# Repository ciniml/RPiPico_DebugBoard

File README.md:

# Raspberry Pi Pico Debug Board

## 概要

Raspberry Pi Pico用のデバッグ用ボード。

ブレッドボードを使うほどでもないが、デバッガはつなぎたい もしくはPicoprobeのデバッグ・ユニットとして使いたい場合に便利なように配線を引き出すためのボードです。

[回路図(PDF)](./RPiPico_SimpleBoard.pdf)

## 特徴

* リセット・スイッチ
* Picoprobe用SWD + UART TX/RXコネクタ
* デバッガ接続用ポゴピン実装スルーホール
* 全信号2列引き出し
  * 信号引き出しつつ、ロジックアナライザを接続可能

## 使用例

### RPi Picoを2枚つかったSWDデバッグ

上側のデバッグ基板のファームウェアとして [`rust-dap`](https://github.com/ciniml/rust-dap) を書き込み。下側のRaspberry Pi PicoにLチカファームウェアをデバッガ経由で書き込んでデバッグ中

## ライセンス

### 基板本体
CC BY 4.0
<br />This work is licensed under a <a rel="license" href="http://creativecommons.org/licenses/by/4.0/">Creative Commons Attribution 4.0 International License</a>.

### ライブラリ (local.kicad_sym, local.pretty以下)

一部のコンポーネントがKiCad標準のコンポーネントを改変したものであるため、そのライセンス (CC BY-SA 4.0) が適用される

また、Raspberry Pi Picoの3Dモデルも、CC BY-SA 4.0に基いて配布されているので同様である。
https://www.raspberrypi.com/documentation/microcontrollers/raspberry-pi-pico.html

CC BY-SA 4.0
<br />This work is licensed under a <a rel="license" href="http://creativecommons.org/licenses/by-sa/4.0/">Creative Commons Attribution-ShareAlike 4.0 International License</a>.

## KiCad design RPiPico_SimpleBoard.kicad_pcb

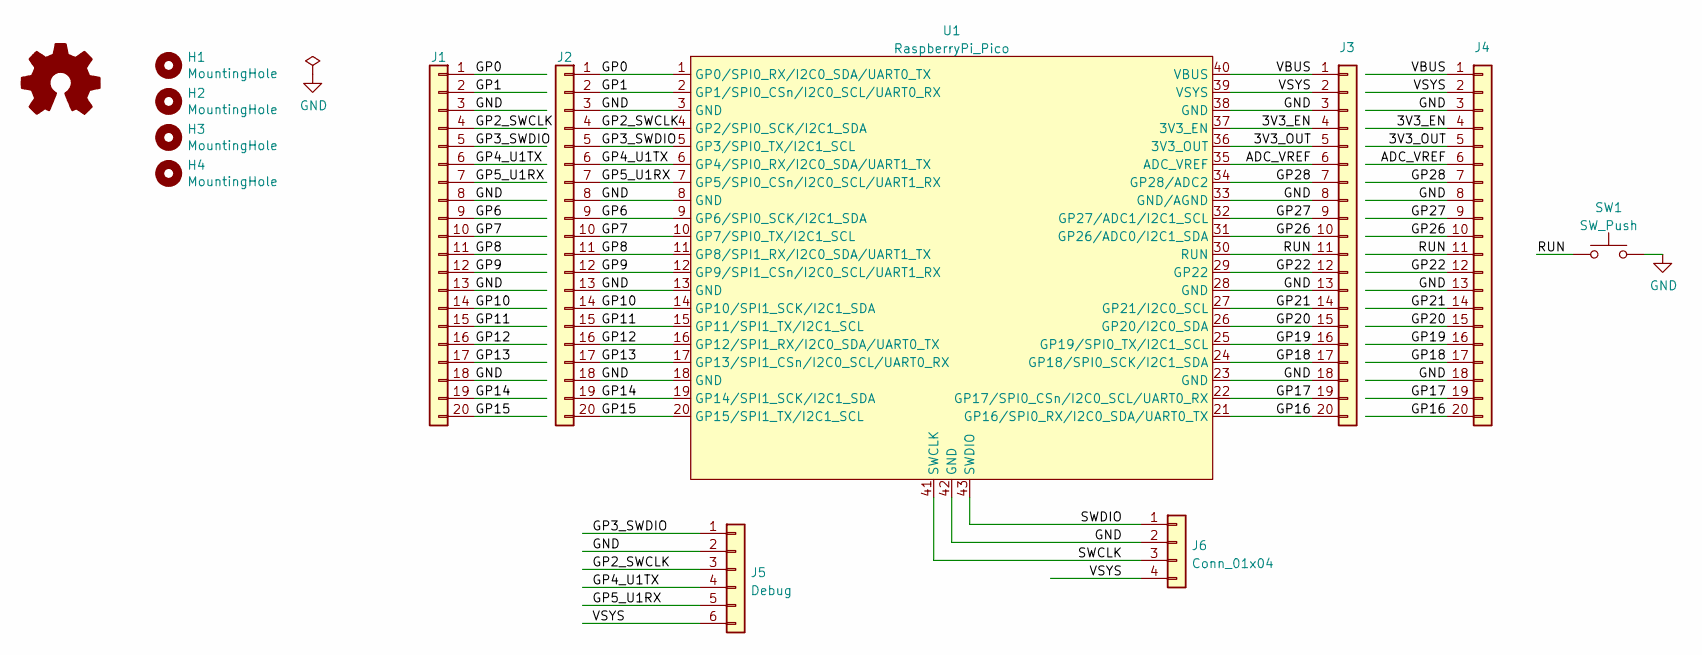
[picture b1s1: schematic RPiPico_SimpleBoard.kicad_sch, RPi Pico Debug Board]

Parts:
H1, H2, H3, H4: MountingHole; MountingHole_3.2mm_M3
J1, J4: Conn_01x20; PinHeader_1x20_P2.54mm_Vertical_Narrow
J2, J3: Conn_01x20; PinSocket_1x20_P2.54mm_Vertical_Narrow
J5: Debug; PinHeader_1x06_P2.54mm_Horizontal_Narrow
J6: Conn_01x04; PinHeader_1x04_P2.54mm_Vertical
LOGO1: Logo_Open_Hardware_Small; logo
SW1: SW_Push; TVBP06-BN043XX-B
U1: RaspberryPi_Pico; Raspberry_Pi_Pico_TH_SMD_SWD

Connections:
/3V3_EN: J3.4, J4.4, U1.37 (3V3_EN)
/3V3_OUT: J3.5, J4.5, U1.36 (3V3_OUT)
/ADC_VREF: J3.6, J4.6, U1.35 (ADC_VREF)
/GP0: J1.1, J2.1, U1.1 (GP0/SPI0_RX/I2C0_SDA/UART0_TX)
/GP1: J1.2, J2.2, U1.2 (GP1/SPI0_CSn/I2C0_SCL/UART0_RX)
/GP2_SWCLK: J1.4, J2.4, J5.3, U1.4 (GP2/SPI0_SCK/I2C1_SDA)
/GP3_SWDIO: J1.5, J2.5, J5.1, U1.5 (GP3/SPI0_TX/I2C1_SCL)
/GP4_U1TX: J1.6, J2.6, J5.4, U1.6 (GP4/SPI0_RX/I2C0_SDA/UART1_TX)
/GP5_U1RX: J1.7, J2.7, J5.5, U1.7 (GP5/SPI0_CSn/I2C0_SCL/UART1_RX)
/GP6: J1.9, J2.9, U1.9 (GP6/SPI0_SCK/I2C1_SDA)
/GP7: J1.10, J2.10, U1.10 (GP7/SPI0_TX/I2C1_SCL)
/GP8: J1.11, J2.11, U1.11 (GP8/SPI1_RX/I2C0_SDA/UART1_TX)
/GP9: J1.12, J2.12, U1.12 (GP9/SPI1_CSn/I2C0_SCL/UART1_RX)
/GP10: J1.14, J2.14, U1.14 (GP10/SPI1_SCK/I2C1_SDA)
/GP11: J1.15, J2.15, U1.15 (GP11/SPI1_TX/I2C1_SCL)
/GP12: J1.16, J2.16, U1.16 (GP12/SPI1_RX/I2C0_SDA/UART0_TX)
/GP13: J1.17, J2.17, U1.17 (GP13/SPI1_CSn/I2C0_SCL/UART0_RX)
/GP14: J1.19, J2.19, U1.19 (GP14/SPI1_SCK/I2C1_SDA)
/GP15: J1.20, J2.20, U1.20 (GP15/SPI1_TX/I2C1_SCL)
/GP16: J3.20, J4.20, U1.21 (GP16/SPI0_RX/I2C0_SDA/UART0_TX)
/GP17: J3.19, J4.19, U1.22 (GP17/SPI0_CSn/I2C0_SCL/UART0_RX)
/GP18: J3.17, J4.17, U1.24 (GP18/SPI0_SCK/I2C1_SDA)
/GP19: J3.16, J4.16, U1.25 (GP19/SPI0_TX/I2C1_SCL)
/GP20: J3.15, J4.15, U1.26 (GP20/I2C0_SDA)
/GP21: J3.14, J4.14, U1.27 (GP21/I2C0_SCL)
/GP22: J3.12, J4.12, U1.29 (GP22)
/GP26: J3.10, J4.10, U1.31 (GP26/ADC0/I2C1_SDA)
/GP27: J3.9, J4.9, U1.32 (GP27/ADC1/I2C1_SCL)
/GP28: J3.7, J4.7, U1.34 (GP28/ADC2)
/RUN: J3.11, J4.11, SW1.1, U1.30 (RUN)
/SWCLK: J6.3, U1.41 (SWCLK)
/SWDIO: J6.1, U1.43 (SWDIO)
/VBUS: J3.1, J4.1, U1.40 (VBUS)
/VSYS: J3.2, J4.2, J5.6, J6.4, U1.39 (VSYS)
GND: J1.3, J1.8, J1.13, J1.18, J2.3, J2.8, J2.13, J2.18, J3.3, J3.8, J3.13, J3.18, J4.3, J4.8, J4.13, J4.18, J5.2, J6.2, SW1.2, U1.3 (GND), U1.8 (GND), U1.13 (GND), U1.18 (GND), U1.23 (GND), U1.28 (GND), U1.33 (GND/AGND), U1.38 (GND), U1.42 (GND)

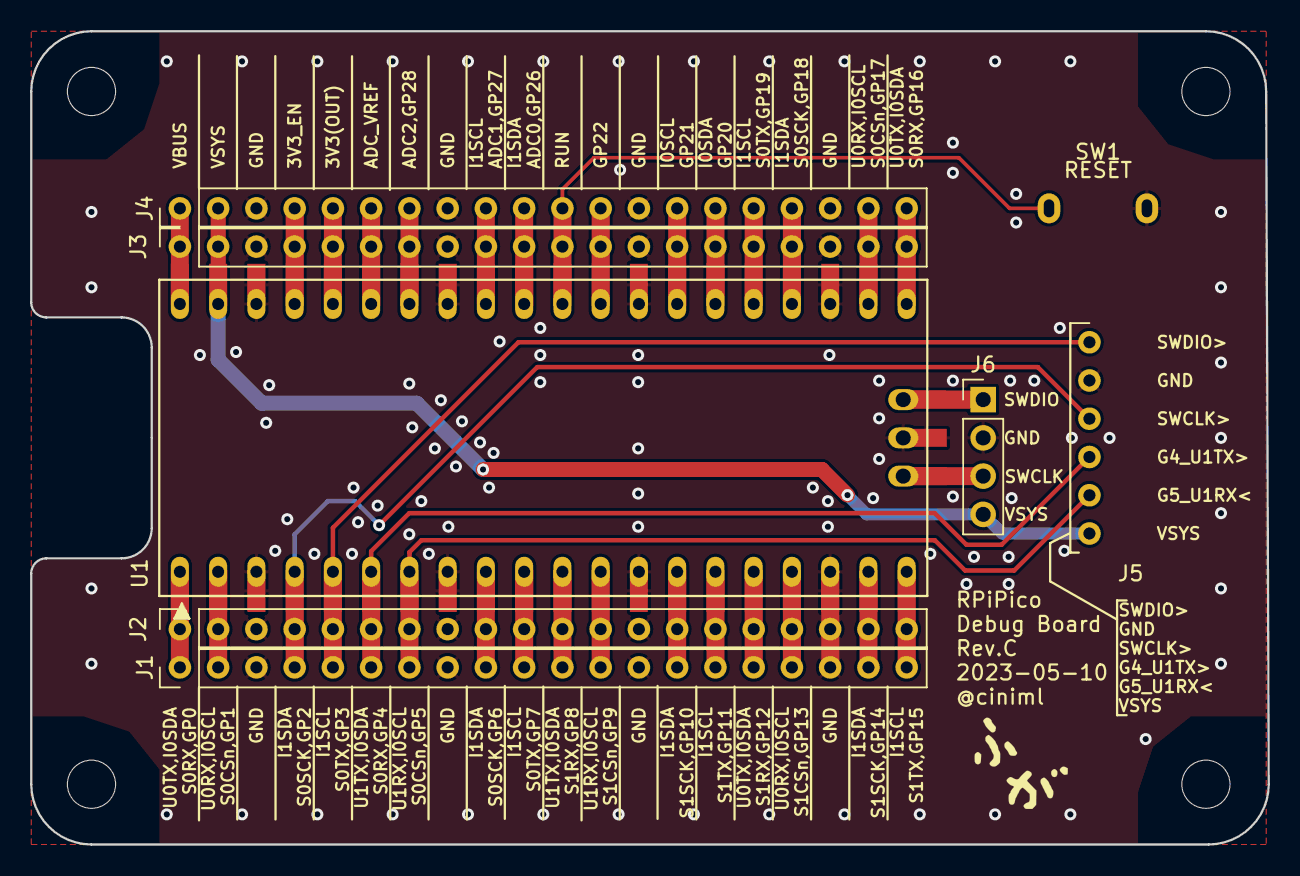
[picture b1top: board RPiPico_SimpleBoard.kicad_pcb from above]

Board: 2 copper layers, 82.2 x 54.0 mm, 13 parts (0 on the bottom side), 35 nets.

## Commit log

2023-02-19 Fix outline not to conflict with USB cables.
2023-02-19 Add license.
2023-05-07 Add SVG files
2023-05-07 Add usage photo.
2023-05-09 fix some silk prints
    (GP5) U0RX -> U1RX
    (GP26) I1SCL -> I1SDA
    (GP21) GP20 -> GP21
2023-05-10 Rev.C
